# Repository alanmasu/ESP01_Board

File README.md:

# ESP01 Board
## Description
This board is inspired from the classic ESP01 Relay board. 
In the large case of Relay boards, you can find the same problems like the relay is driven LOW end when the ESP boots up, the relay is triggered since the ESP boot reaches the end of the setup function when the GPIO pin is set to LOW.

The ESP01 Board is designed to solve these problems, but also to provide a more stable and flexible solution for your projects.

The output stage of strapping pins is latched and modifyng the time constant of the RC (R12-C7 and R13-C8) you can change the time of the latching. The default latched time is about 210ms for certain, but the latces become transparent after 545ms due to the $V_{IL}$ of the Latch is $0,9V$ so the latch is completally transparent when the RC circuit reaches $0,9V$; in the range of $2V - 0,9V$ the behavior of the latch is unpredictable.

## Features
- ESP01/ESP01-S Module
- 1x Relay 5V or 3.3V (hardware configurable whit a jumper)
- 2x NMOS Output Stage, 
- 2x NMOS Latched Output Stage,
- 4x Input Stage, with 2 of them pulled up to 3.3V with a 10K resistor,
- 1x 3.3V LDO Regulator,
- 1x fuse for the 5V input,
- USB Type-C Connector for power supply (or a classic pin header).

## Note
> If you need the UART pins, you can use the I1 and I3 pins but you need to remove the 10K resistor (R2 and R3) and the NMOS (Q1 and Q2) from the board.

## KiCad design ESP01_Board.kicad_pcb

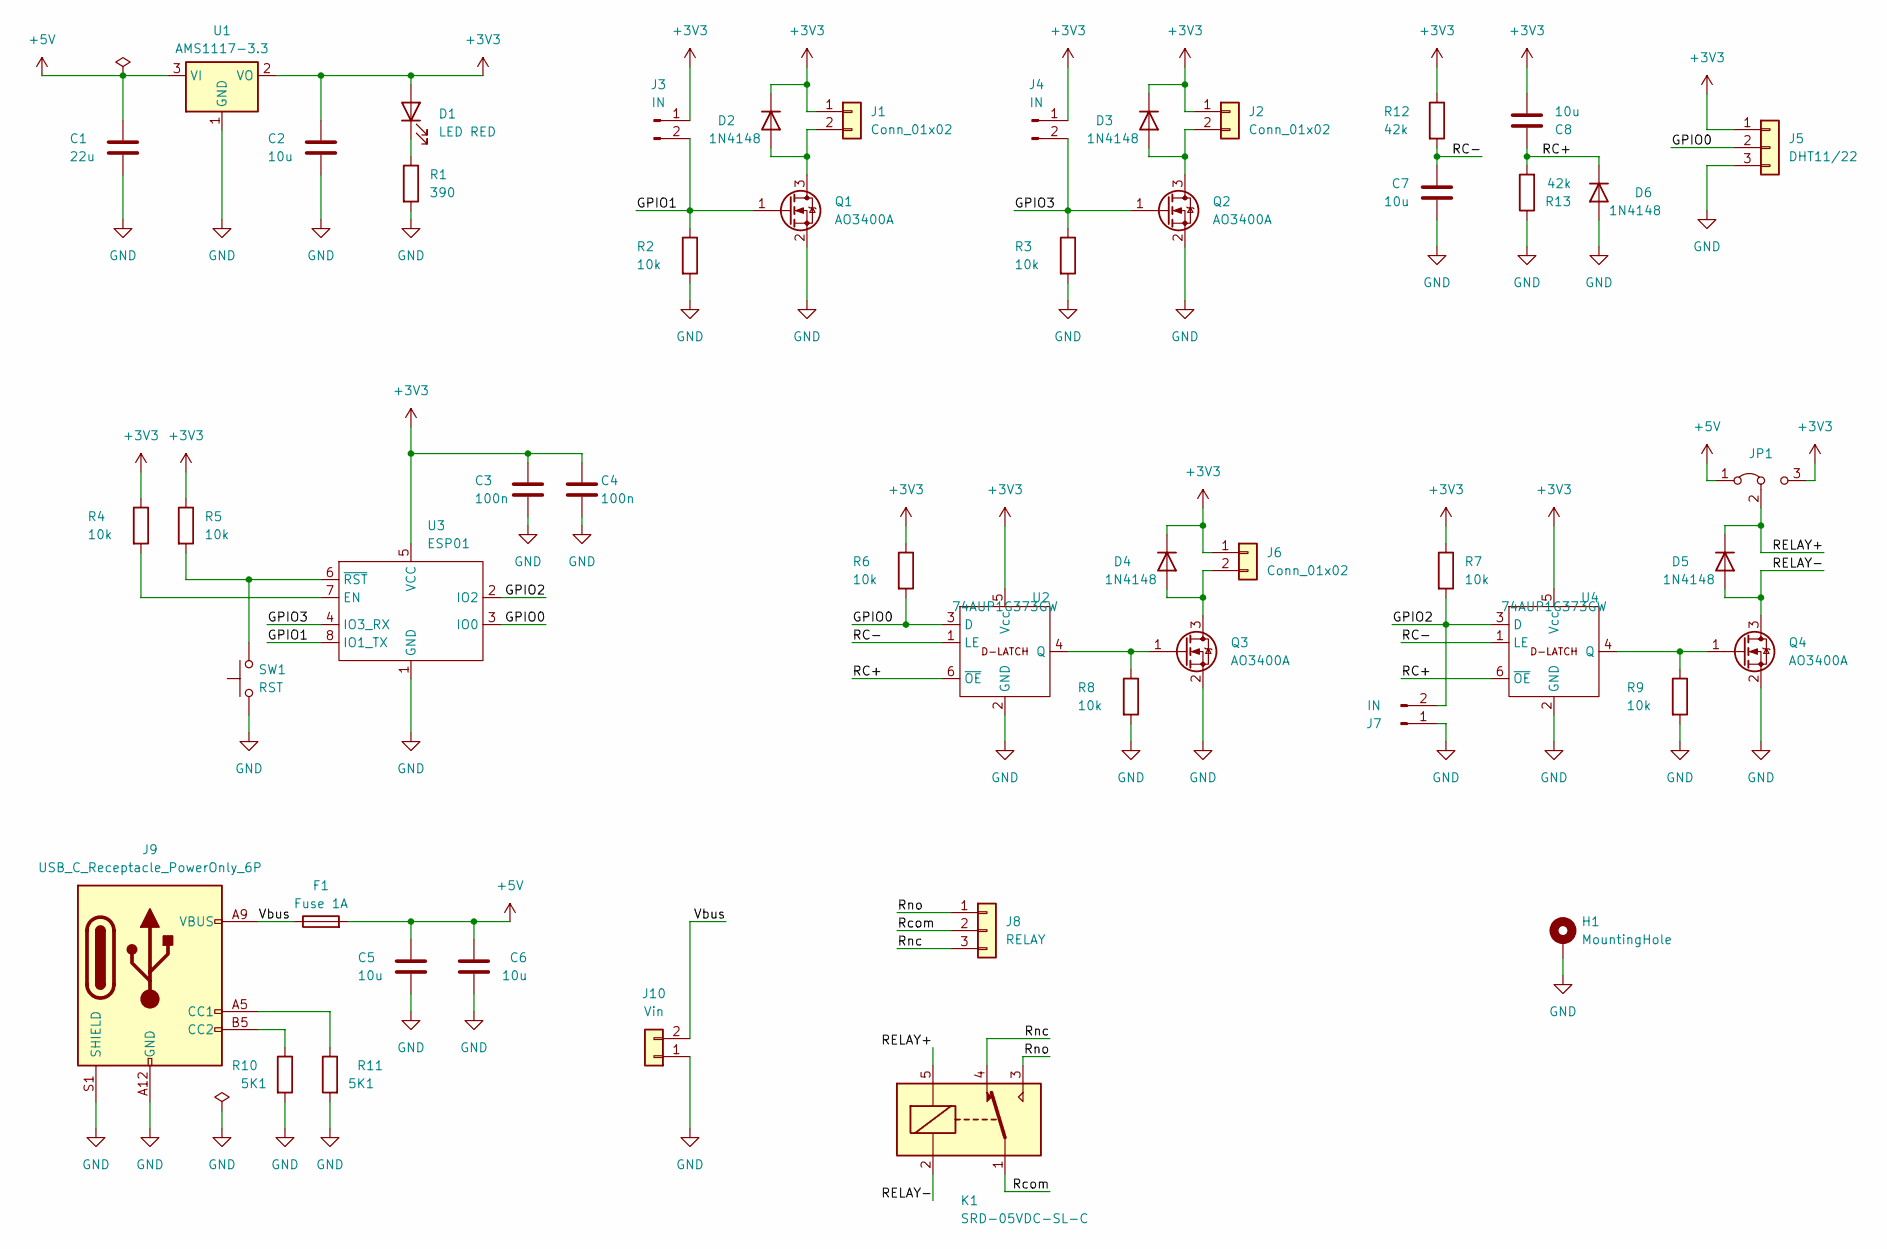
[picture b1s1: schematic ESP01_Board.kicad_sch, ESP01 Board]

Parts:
C1: 22u; C_0805_2012Metric
C2, C5, C6, C7, C8: 10u; C_0805_2012Metric
C3, C4: 100n; C_0805_2012Metric
D1: LED RED; D_0805_2012Metric_Pad1.15x1.40mm_HandSolder
D2, D3, D4, D5, D6: 1N4148; D_SOD-123
F1: Fuse 1A; Fuse_0805_2012Metric_Pad1.15x1.40mm_HandSolder
H1: MountingHole; MountingHole_3.2mm_M3_ISO14580_Pad
J1, J2, J6: Conn_01x02; PinHeader_1x02_P2.54mm_Vertical
J3, J4, J7: IN; PinHeader_SMD_1x02_P2.54
J5: DHT11/22; PinHeader_1x03_P2.54mm_Vertical
J8: RELAY; PinHeader_1x03_P2.54mm_Vertical
J9: USB_C_Receptacle_PowerOnly_6P; USB_C_Receptacle_GCT_USB4125-xx-x_6P_TopMnt_Horizontal
J10: Vin; PinHeader_1x02_P2.54mm_Vertical
JP1: Jumper_3_Bridged12; SolderJumper-3_P1.3mm_Bridged12_Pad1.0x1.5mm
K1: SRD-05VDC-SL-C; Relay_SPDT_SANYOU_SRD_Series_Form_C
Q1, Q2, Q3, Q4: AO3400A; SOT-23
R1: 390; R_0805_2012Metric
R2, R3, R4, R5, R6, R7, R8, R9: 10k; R_0805_2012Metric
R10, R11: 5K1; R_0805_2012Metric
R12, R13: 42k; R_0805_2012Metric
SW1: RST; SW_PUSH_1P1T_6x3.5mm_H5.0_APEM_MJTP1250
U1: AMS1117-3.3; SOT-223-3_TabPin2
U2, U4: 74AUP1G373GW; SOT-363_SC-70-6
U3: ESP01

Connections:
+3V3: C2.1, C3.1, C4.1, C8.2, D1.2 (A), D2.1 (K), D3.1 (K), D4.1 (K), J1.1, J2.1, J3.1, J4.1, J5.1, J6.1, JP1.3 (B), R4.1, R5.1, R6.1, R7.1, R12.1, U1.2 (VO), U2.5 (Vcc), U3.5 (VCC), U4.5 (Vcc)
+5V: C1.1, C5.1, C6.1, F1.2, JP1.1 (A), U1.3 (VI)
/GPIO0: J5.2, R6.2, U2.3 (D), U3.3 (IO0)
/GPIO1: J3.2, Q1.1 (G), R2.1, U3.8 (IO1_TX)
/GPIO2: J7.2, R7.2, U3.2 (IO2), U4.3 (D)
/GPIO3: J4.2, Q2.1 (G), R3.1, U3.4 (IO3_RX)
/RC+: C8.1, D6.1 (K), R13.2, U2.6 (~OE), U4.6 (~OE)
/RC-: C7.1, R12.2, U2.1 (LE), U4.1 (LE)
/RELAY+: D5.1 (K), JP1.2 (C), K1.5
/RELAY-: D5.2 (A), K1.2, Q4.3 (D)
/Rcom: J8.2, K1.1
/Rnc: J8.3, K1.4
/Rno: J8.1, K1.3
/Vbus: F1.1, J9.A9 (VBUS), J9.B9 (VBUS), J10.2
GND: C1.2, C2.2, C3.2, C4.2, C5.2, C6.2, C7.2, D6.2 (A), H1.1, J5.3, J7.1, J9.A12 (GND), J9.B12 (GND), J9.S1 (SHIELD), J10.1, Q1.2 (S), Q2.2 (S), Q3.2 (S), Q4.2 (S), R1.2, R2.2, R3.2, R8.2, R9.2, R10.2, R11.2, R13.1, SW1.1, U1.1 (GND), U2.2 (GND), U3.1 (GND), U4.2 (GND)
unnamed: D1.1 (K), R1.1
unnamed: D2.2 (A), J1.2, Q1.3 (D)
unnamed: D3.2 (A), J2.2, Q2.3 (D)
unnamed: D4.2 (A), J6.2, Q3.3 (D)
unnamed: J9.A5 (CC1), R11.1
unnamed: J9.B5 (CC2), R10.1
unnamed: Q3.1 (G), R8.1, U2.4 (Q)
unnamed: Q4.1 (G), R9.1, U4.4 (Q)
unnamed: R4.2, U3.7 (EN)
unnamed: R5.2, SW1.2, U3.6 (~RST)

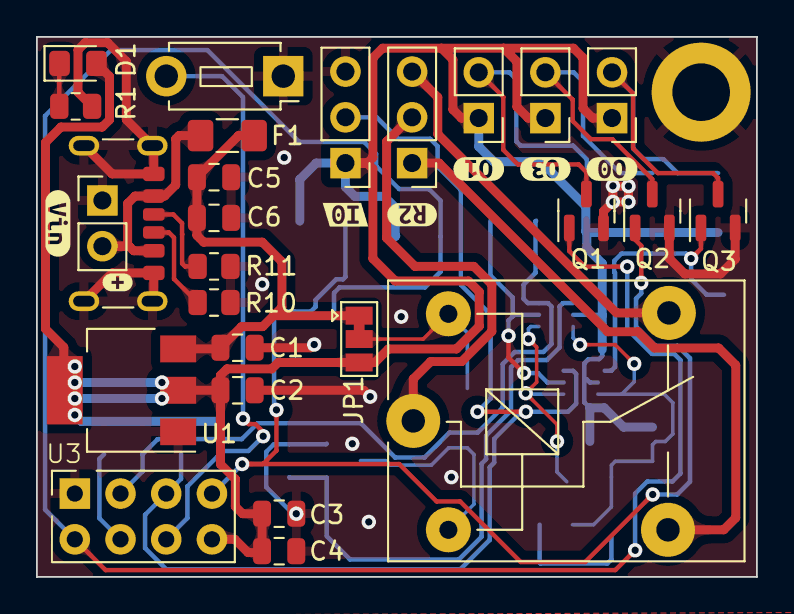
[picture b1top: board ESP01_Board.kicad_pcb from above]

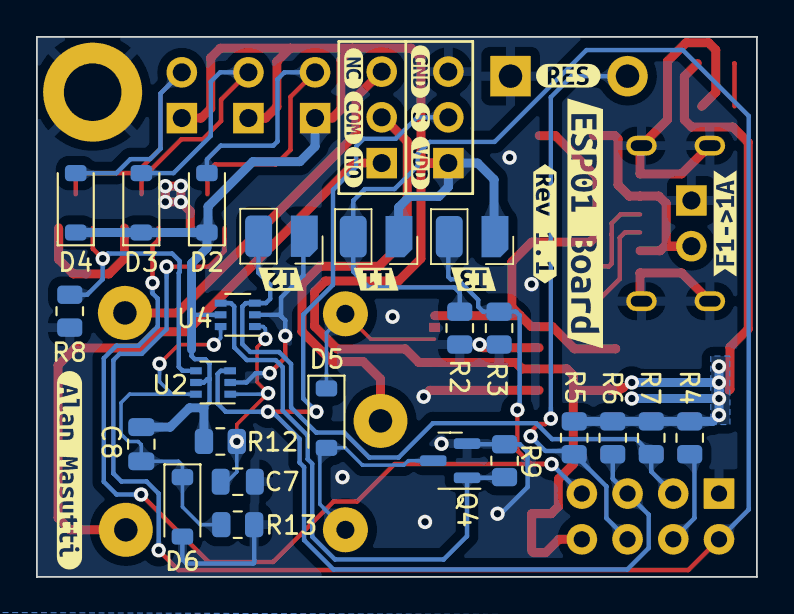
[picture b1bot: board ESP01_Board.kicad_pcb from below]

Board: 2 copper layers, 40.0 x 30.0 mm, 71 parts (37 on the bottom side), 25 nets.

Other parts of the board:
kibuzzard-666D62C0: G***; kibuzzard-666D62C0
kibuzzard-666D62C8: G***; kibuzzard-666D62C8
kibuzzard-666D62F4: G***; kibuzzard-666D62F4
kibuzzard-666D66A3: G***; kibuzzard-666D66A3
kibuzzard-666D627E: G***; kibuzzard-666D627E
kibuzzard-666D664B: G***; kibuzzard-666D664B
kibuzzard-666D6245: G***; kibuzzard-666D6245
kibuzzard-666D6261: G***; kibuzzard-666D6261
kibuzzard-666D6272: G***; kibuzzard-666D6272
kibuzzard-666D6286: G***; kibuzzard-666D6286
kibuzzard-666D6307: G***; kibuzzard-666D6307
kibuzzard-666D6618: G***; kibuzzard-666D6618
kibuzzard-666D6651: G***; kibuzzard-666D6651
kibuzzard-666D6656: G***; kibuzzard-666D6656
kibuzzard-666FE76E: G***; kibuzzard-666FE76E
kibuzzard-6669B1E4: G***; kibuzzard-6669B1E4
kibuzzard-6669B4DA: G***; kibuzzard-6669B4DA
kibuzzard-6669B4F4: G***; kibuzzard-6669B4F4
kibuzzard-6669B213: G***; kibuzzard-6669B213
kibuzzard-6669B231: G***; kibuzzard-6669B231
kibuzzard-6669B493: G***; kibuzzard-6669B493

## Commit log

2024-06-12 First commit + Added License
    Added the project to GIT
2024-06-12 First commit
    Added the project to GIT
2024-06-12 Aggiunti i teardrops
2024-06-12 Modificato lo stadio di ingresso
    - Aggiunti i D-latch per l'utilizzo dei due GPIO di strapping
    - Corretto il Cartiglio dello schematico e compilato quello del foglio del PCB
2024-06-12 Conclusa la prima versione
    - Inserite le serigrafie e controllato il circuito
2024-06-12 Cambiati i footprint ai due Latch
    - Probabilmente ho fatto altre modifiche grafiche alla scheda,
    - Ho fatto delle stampe dei layer quindi anche sulle impostazioni qualcosa può essere cambiato
2024-06-12 Aggiunto il README [TO FINISH
2024-06-12 Aggiunti i codici LCSC + Aggiornato footprint del fuse
    - Aggiunta anche la serigrafia con il valore del fusibile,
    - Aggiornata la data sul foglio del PCB,
    - Ricreati i teardrop
2024-06-12 Completata Rev1.1
    - Sistemati Errori di sovrascritture (Vedi ad esempio i cartigli)
    - Sistemata la BOM
    - Corrette le Serigrafie
    - Controllato il design
2024-06-12 Aggiunte le esclusioni DRC
